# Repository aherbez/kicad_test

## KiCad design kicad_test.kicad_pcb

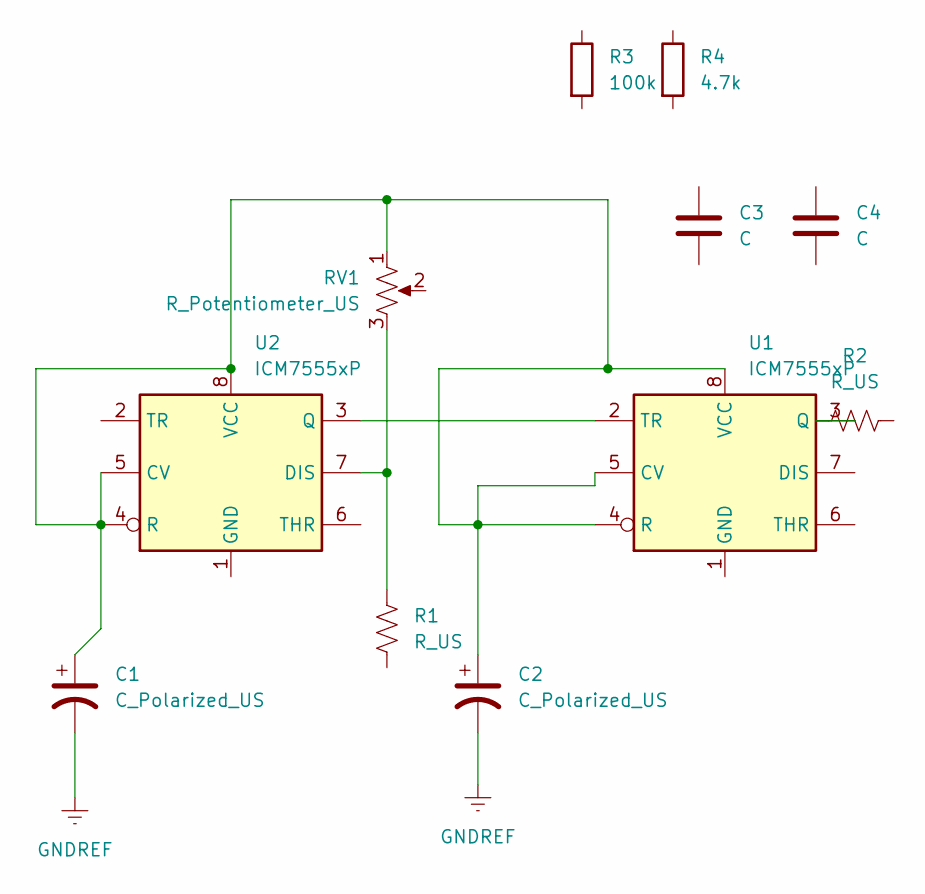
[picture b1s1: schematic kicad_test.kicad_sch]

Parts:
C1, C2: C_Polarized_US; CP_Axial_L10.0mm_D4.5mm_P15.00mm_Horizontal
C3, C4: C; CP_Axial_L10.0mm_D4.5mm_P15.00mm_Horizontal
R1, R2: R_US; R_Axial_DIN0204_L3.6mm_D1.6mm_P1.90mm_Vertical
R3: 100k; R_Axial_DIN0411_L9.9mm_D3.6mm_P12.70mm_Horizontal
R4: 4.7k; R_Axial_DIN0204_L3.6mm_D1.6mm_P1.90mm_Vertical
RV1: R_Potentiometer_US
U1, U2: ICM7555xP; DIP-8_W7.62mm

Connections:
GNDREF: C1.2, C2.2
unnamed: C1.1, C2.1, RV1.1, U1.4 (R), U1.5 (CV), U1.8 (VCC), U2.4 (R), U2.5 (CV), U2.8 (VCC)
unnamed: R2.1, U1.3 (Q)
unnamed: U1.2 (TR), U2.3 (Q)
unnamed: R1.1, RV1.3, U2.7 (DIS)

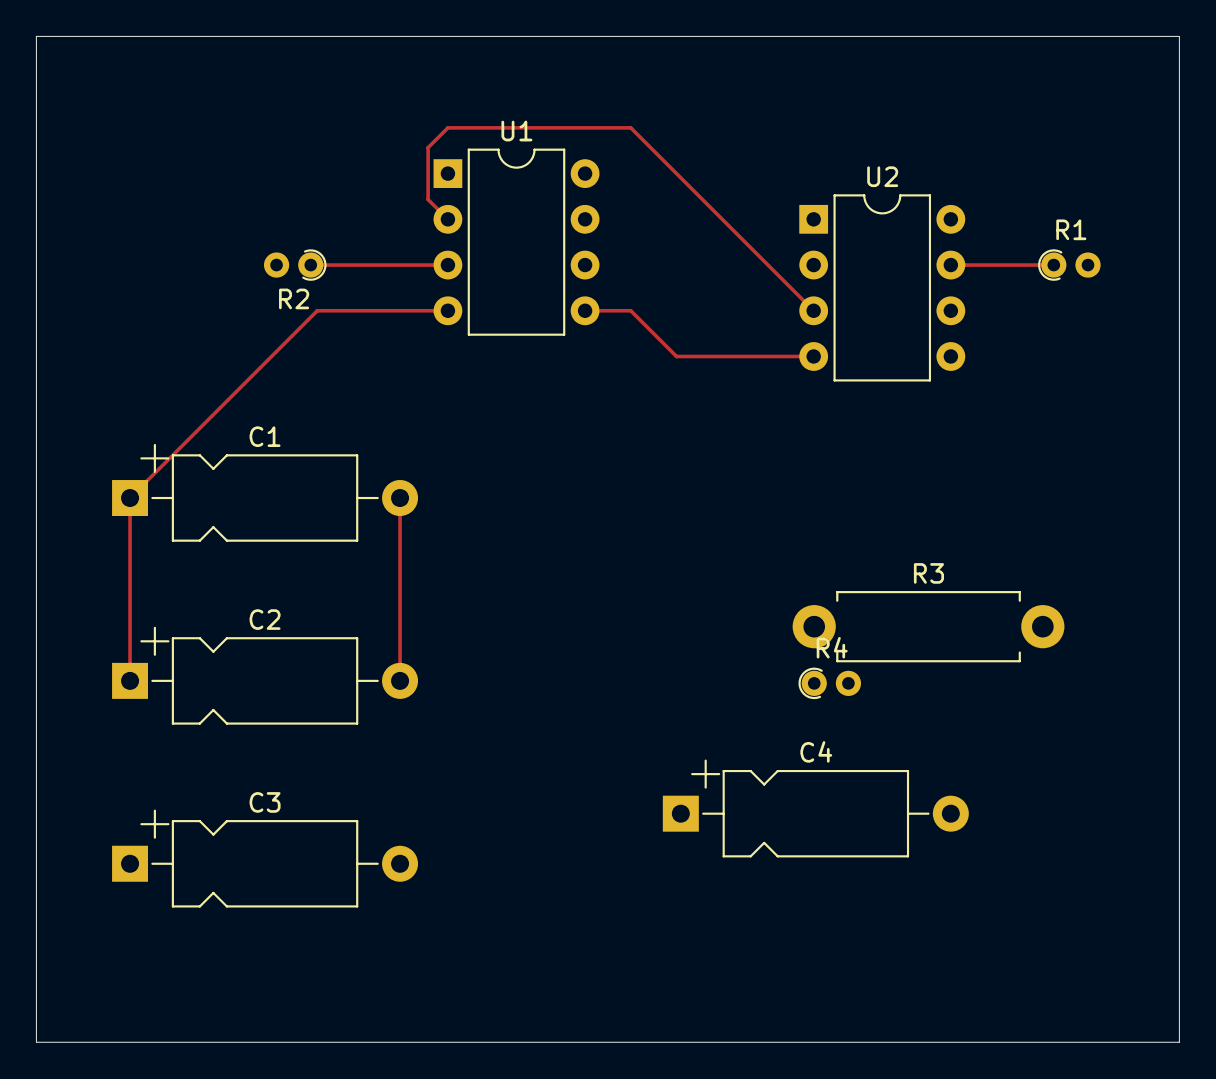
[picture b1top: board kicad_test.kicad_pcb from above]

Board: 2 copper layers, 63.5 x 55.9 mm, 10 parts (0 on the bottom side), 5 nets.

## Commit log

2025-01-06 adding blank pcb
2025-01-06 Revert "adding blank pcb"
    This reverts commit 8b02b26090363cbf4832f459a13609c0179bd66e.
2025-01-06 adding pcb
2025-01-08 couple changes
2025-01-08 tweaking resistors
2025-01-09 blank pcb
2025-01-10 adding footprints for R and Cs
2025-01-10 updating pcb from schematic
2025-01-10 moving parts in pcb
2025-01-10 adding edge cut rect
2025-01-10 adding first traces
2025-01-21 basic schematic changes
2025-01-27 adding two-point trace
2025-01-27 add and remove trace
2025-05-19 updating to KiCAD 9
2025-07-10 changing fill in symbol
